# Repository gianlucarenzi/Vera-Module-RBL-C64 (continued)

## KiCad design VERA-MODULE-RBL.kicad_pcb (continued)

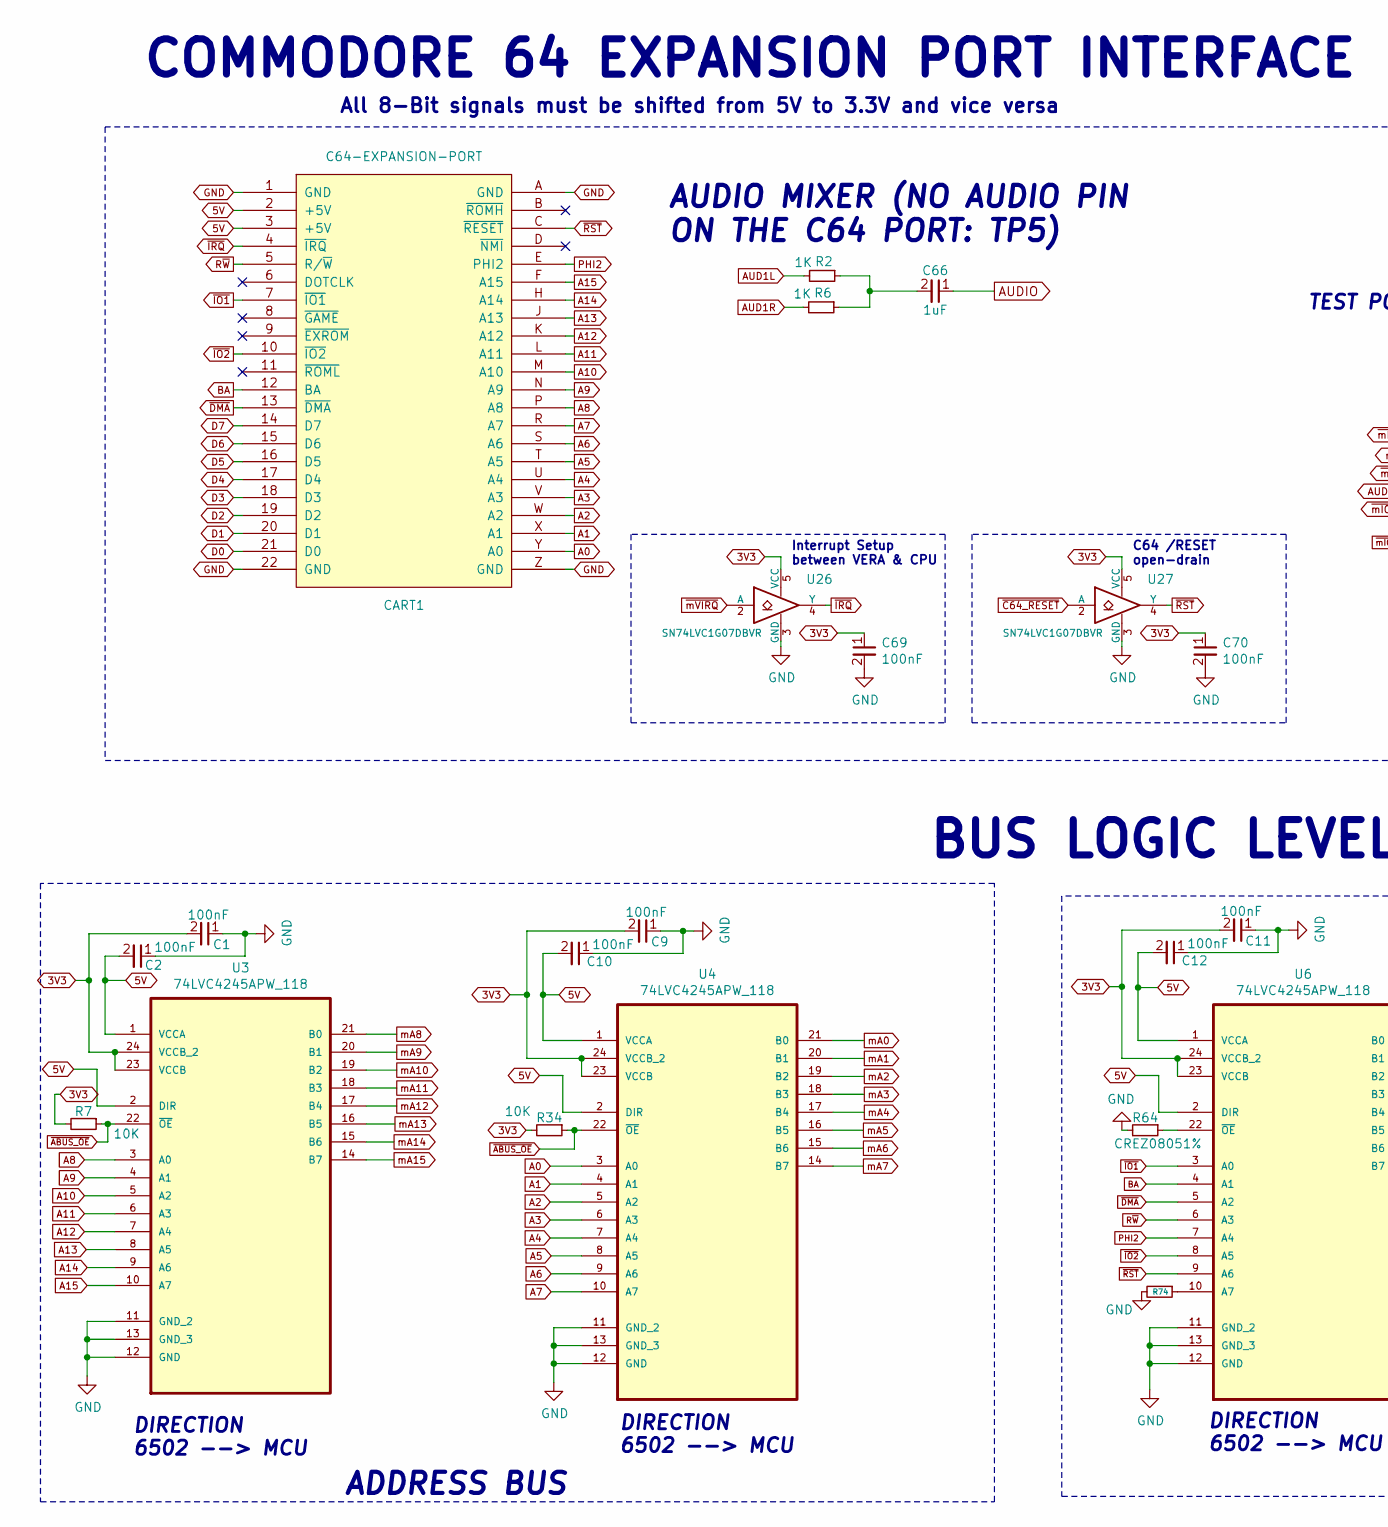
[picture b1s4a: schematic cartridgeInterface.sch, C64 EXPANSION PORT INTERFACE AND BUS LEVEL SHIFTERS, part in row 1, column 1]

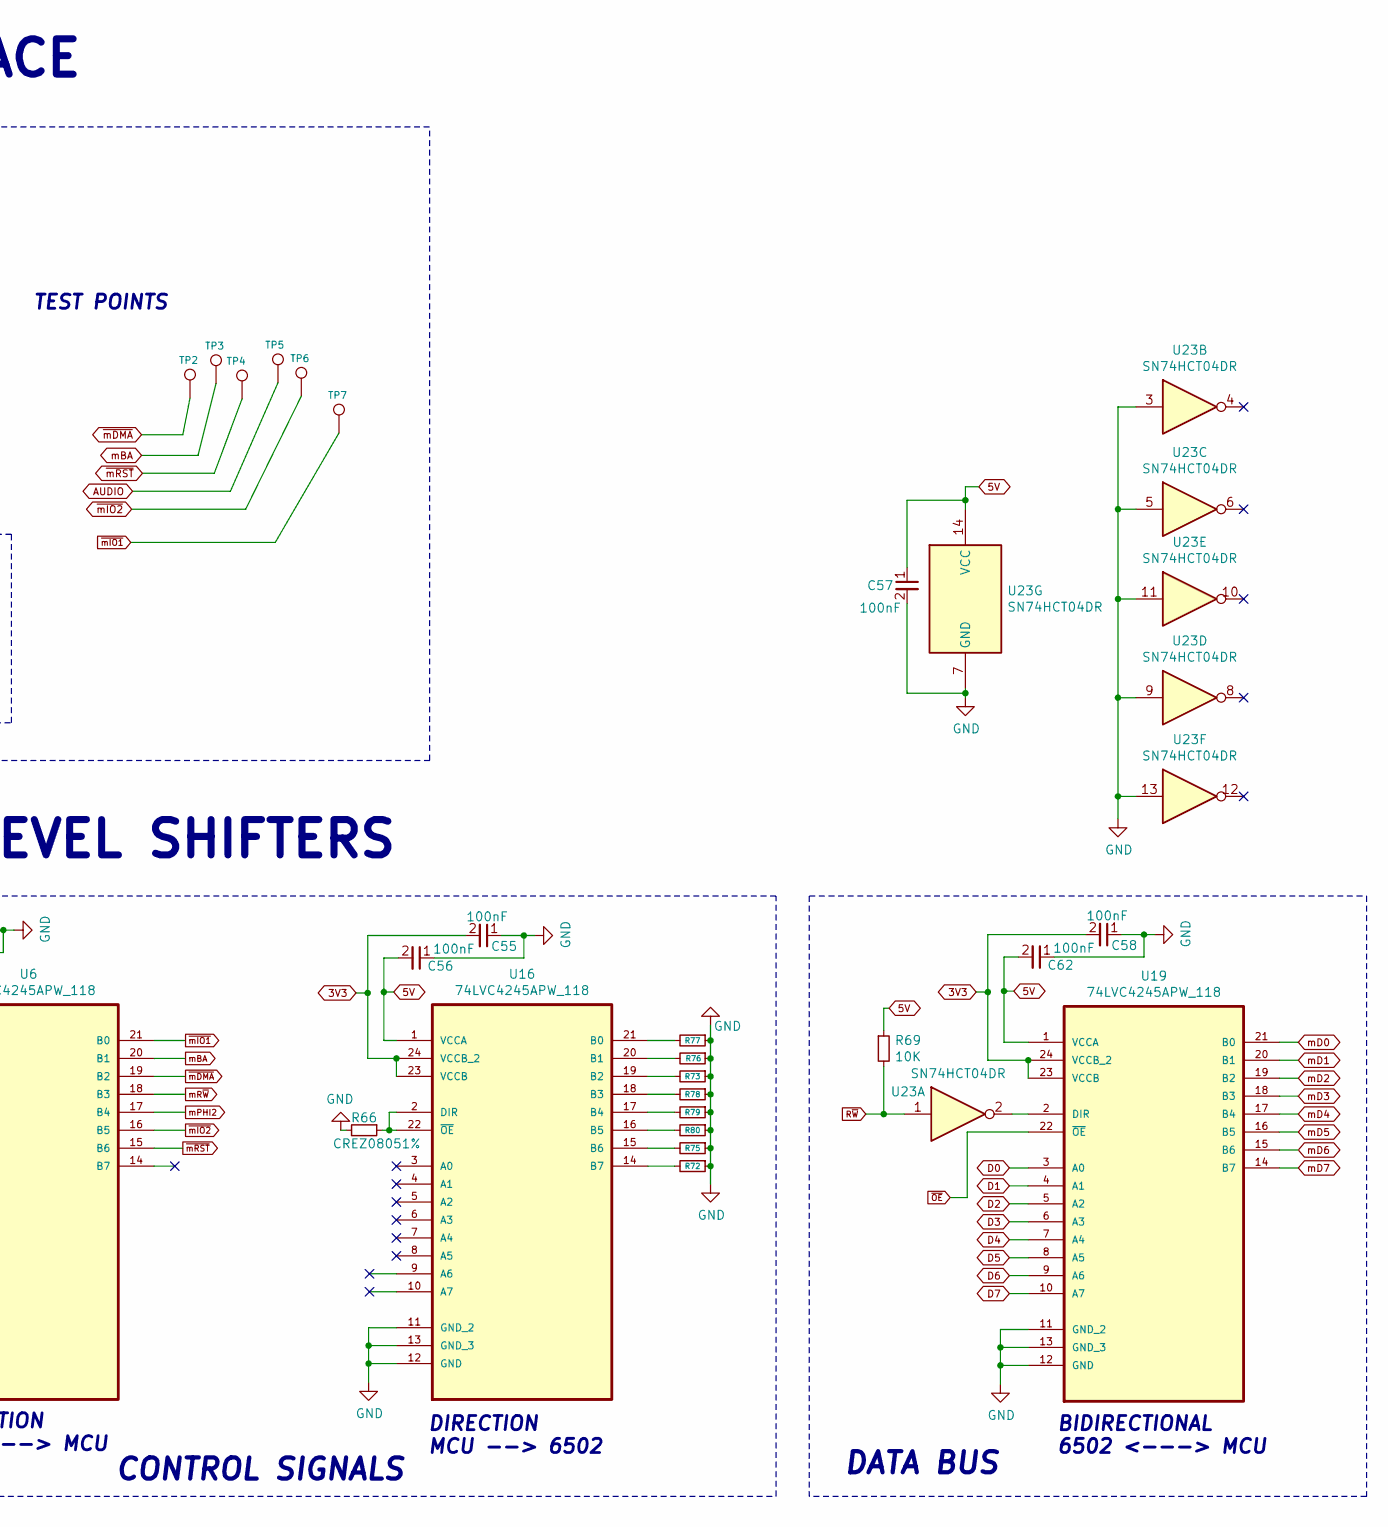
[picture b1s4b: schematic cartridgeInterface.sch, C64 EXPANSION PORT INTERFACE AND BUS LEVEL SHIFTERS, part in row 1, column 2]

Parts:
C1, C2, C9, C10, C11, C12, C55, C56, C57, C58, C62, C69, C70: 100nF; C_0805_2012Metric_Pad1.18x1.45mm_HandSolder; LCSC C28233
C66: 1uF; C_0805_2012Metric_Pad1.18x1.45mm_HandSolder; LCSC C28323
CART1: C64-EXPANSION-PORT; C64-EXPANSION-CARTRIDGE
R2, R6: 1K; R_0805_2012Metric_Pad1.20x1.40mm_HandSolder; LCSC C17513
R7, R34, R69: 10K; R_0805_2012Metric_Pad1.20x1.40mm_HandSolder; LCSC C17414
R64, R66, R72, R73, R74, R75, R76, R77, R78, R79, R80: CREZ08051%; R_0805_2012Metric_Pad1.20x1.40mm_HandSolder; LCSC C17477
TP2, TP3, TP4, TP5, TP6, TP7: TestPoint; TestPoint_Pad_D2.0mm
U3, U4, U6, U16, U19: 74LVC4245APW_118; IC_74LVC4245_SOP65P640X110-24N; LCSC C6091
U23: SN74HCT04DR; SOIC-14_3.9x8.7mm_P1.27mm; LCSC C6766
U26, U27: SN74LVC1G07DBVR; SOT-23-5; LCSC C7829

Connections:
3V3: C1.2, C9.2, C11.2, C55.2, C58.2, C69.1, C70.1, R7.2, R34.2, U3.23 (VCCB), U3.24 (VCCB_2), U4.23 (VCCB), U4.24 (VCCB_2), U6.23 (VCCB), U6.24 (VCCB_2), U16.23 (VCCB), U16.24 (VCCB_2), U19.23 (VCCB), U19.24 (VCCB_2), U26.5 (VCC), U27.5 (VCC); also elsewhere on the board
5V: C2.2, C10.2, C12.2, C56.2, C57.1, C62.2, CART1.2 (+5V), CART1.3 (+5V), R69.1, U3.1 (VCCA), U3.2 (DIR), U4.1 (VCCA), U4.2 (DIR), U6.1 (VCCA), U6.2 (DIR), U16.1 (VCCA), U19.1 (VCCA), U23.14 (VCC); also elsewhere on the board
A0: CART1.Y (A0), U4.3 (A0)
A1: CART1.X (A1), U4.4 (A1)
A2: CART1.W (A2), U4.5 (A2)
A3: CART1.V (A3), U4.6 (A3)
A4: CART1.U (A4), U4.7 (A4)
A5: CART1.T (A5), U4.8 (A5)
A6: CART1.S (A6), U4.9 (A6)
A7: CART1.R (A7), U4.10 (A7)
A8: CART1.P (A8), U3.3 (A0)
A9: CART1.N (A9), U3.4 (A1)
A10: CART1.M (A10), U3.5 (A2)
A11: CART1.L (A11), U3.6 (A3)
A12: CART1.K (A12), U3.7 (A4)
A13: CART1.J (A13), U3.8 (A5)
A14: CART1.H (A14), U3.9 (A6)
A15: CART1.F (A15), U3.10 (A7)
AUD1L: R2.2; also elsewhere on the board
AUD1R: R6.2; also elsewhere on the board
AUDIO: C66.1, TP5.1
BA: CART1.12 (BA), U6.4 (A1)
D0: CART1.21 (D0), U19.3 (A0)
D1: CART1.20 (D1), U19.4 (A1)
D2: CART1.19 (D2), U19.5 (A2)
D3: CART1.18 (D3), U19.6 (A3)
D4: CART1.17 (D4), U19.7 (A4)
D5: CART1.16 (D5), U19.8 (A5)
D6: CART1.15 (D6), U19.9 (A6)
D7: CART1.14 (D7), U19.10 (A7)
GND: C1.1, C2.1, C9.1, C10.1, C11.1, C12.1, C55.1, C56.1, C57.2, C58.1, C62.1, C69.2, C70.2, CART1.1 (GND), CART1.22 (GND), CART1.A (GND), CART1.Z (GND), R64.2, R66.2, R72.1, R73.1, R74.2, R75.1, R76.1, R77.1, R78.1, R79.1, R80.1, U3.11 (GND_2), U3.12 (GND), U3.13 (GND_3), U4.11 (GND_2), U4.12 (GND), U4.13 (GND_3), U6.11 (GND_2), U6.12 (GND), U6.13 (GND_3), U16.11 (GND_2), U16.12 (GND), U16.13 (GND_3), U19.11 (GND_2), U19.12 (GND), U19.13 (GND_3), U23.3, U23.5, U23.7 (GND), U23.9, U23.11, U23.13, U26.3 (GND), U27.3 (GND); also elsewhere on the board
unnamed: C66.2, R2.1, R6.1
unnamed: R64.1, U6.22 (~OE)
unnamed: R66.1, U16.2 (DIR), U16.22 (~OE)
unnamed: R72.2, U16.14 (B7)
unnamed: R73.2, U16.19 (B2)
unnamed: R74.1, U6.10 (A7)
unnamed: R75.2, U16.15 (B6)
unnamed: R76.2, U16.20 (B1)
unnamed: R77.2, U16.21 (B0)
unnamed: R78.2, U16.18 (B3)
unnamed: R79.2, U16.17 (B4)
unnamed: R80.2, U16.16 (B5)
unnamed: U19.2 (DIR), U23.2
PHI2: CART1.E (PHI2), U6.7 (A4)
R~W: CART1.5 (R/~W), R69.2, U6.6 (A3), U23.1
mA0: U4.21 (B0); also elsewhere on the board
mA1: U4.20 (B1); also elsewhere on the board
mA2: U4.19 (B2); also elsewhere on the board
mA3: U4.18 (B3); also elsewhere on the board
mA4: U4.17 (B4); also elsewhere on the board
mA5: U4.16 (B5); also elsewhere on the board
mA6: U4.15 (B6); also elsewhere on the board
mA7: U4.14 (B7); also elsewhere on the board
mA8: U3.21 (B0); also elsewhere on the board
mA9: U3.20 (B1); also elsewhere on the board
mA10: U3.19 (B2); also elsewhere on the board
mA11: U3.18 (B3); also elsewhere on the board
mA12: U3.17 (B4); also elsewhere on the board
mA13: U3.16 (B5); also elsewhere on the board
mA14: U3.15 (B6); also elsewhere on the board
mA15: U3.14 (B7); also elsewhere on the board
mBA: TP3.1, U6.20 (B1)
mD0: U19.21 (B0); also elsewhere on the board
mD1: U19.20 (B1); also elsewhere on the board
mD2: U19.19 (B2); also elsewhere on the board
mD3: U19.18 (B3); also elsewhere on the board
mD4: U19.17 (B4); also elsewhere on the board
mD5: U19.16 (B5); also elsewhere on the board
mD6: U19.15 (B6); also elsewhere on the board
mD7: U19.14 (B7); also elsewhere on the board
mPHI2: U6.17 (B4); also elsewhere on the board
mR~W: U6.18 (B3); also elsewhere on the board
~ABUS_OE: R7.1, R34.1, U3.22 (~OE), U4.22 (~OE); also elsewhere on the board
~C64_RESET: U27.2 (A); also elsewhere on the board
~DMA: CART1.13 (~DMA), U6.5 (A2)
~IO1: CART1.7 (~IO1), U6.3 (A0)
~IO2: CART1.10 (~IO2), U6.8 (A5)
~IRQ: CART1.4 (~IRQ), U26.4 (Y)
~OE: U19.22 (~OE); also elsewhere on the board
~RST: CART1.C (~RESET), U6.9 (A6), U27.4 (Y)
~mDMA: TP2.1, U6.19 (B2)
~mIO1: TP7.1, U6.21 (B0); also elsewhere on the board
~mIO2: TP6.1, U6.16 (B5); also elsewhere on the board
~mRST: TP4.1, U6.15 (B6)
~mVIRQ: U26.2 (A); also elsewhere on the board

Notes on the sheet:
COMMODORE 64 EXPANSION PORT INTERFACE
All 8-Bit signals must be shifted from 5V to 3.3V and vice versa
TEST POINTS
BUS LOGIC LEVEL SHIFTERS
DIRECTION 6502 --> MCU
DIRECTION MCU --> 6502
BIDIRECTIONAL 6502 <---> MCU
CONTROL SIGNALS
ADDRESS BUS
DATA BUS
Interrupt Setup between VERA & CPU
C64 /RESET open-drain
AUDIO MIXER (NO AUDIO PIN ON THE C64 PORT: TP5)

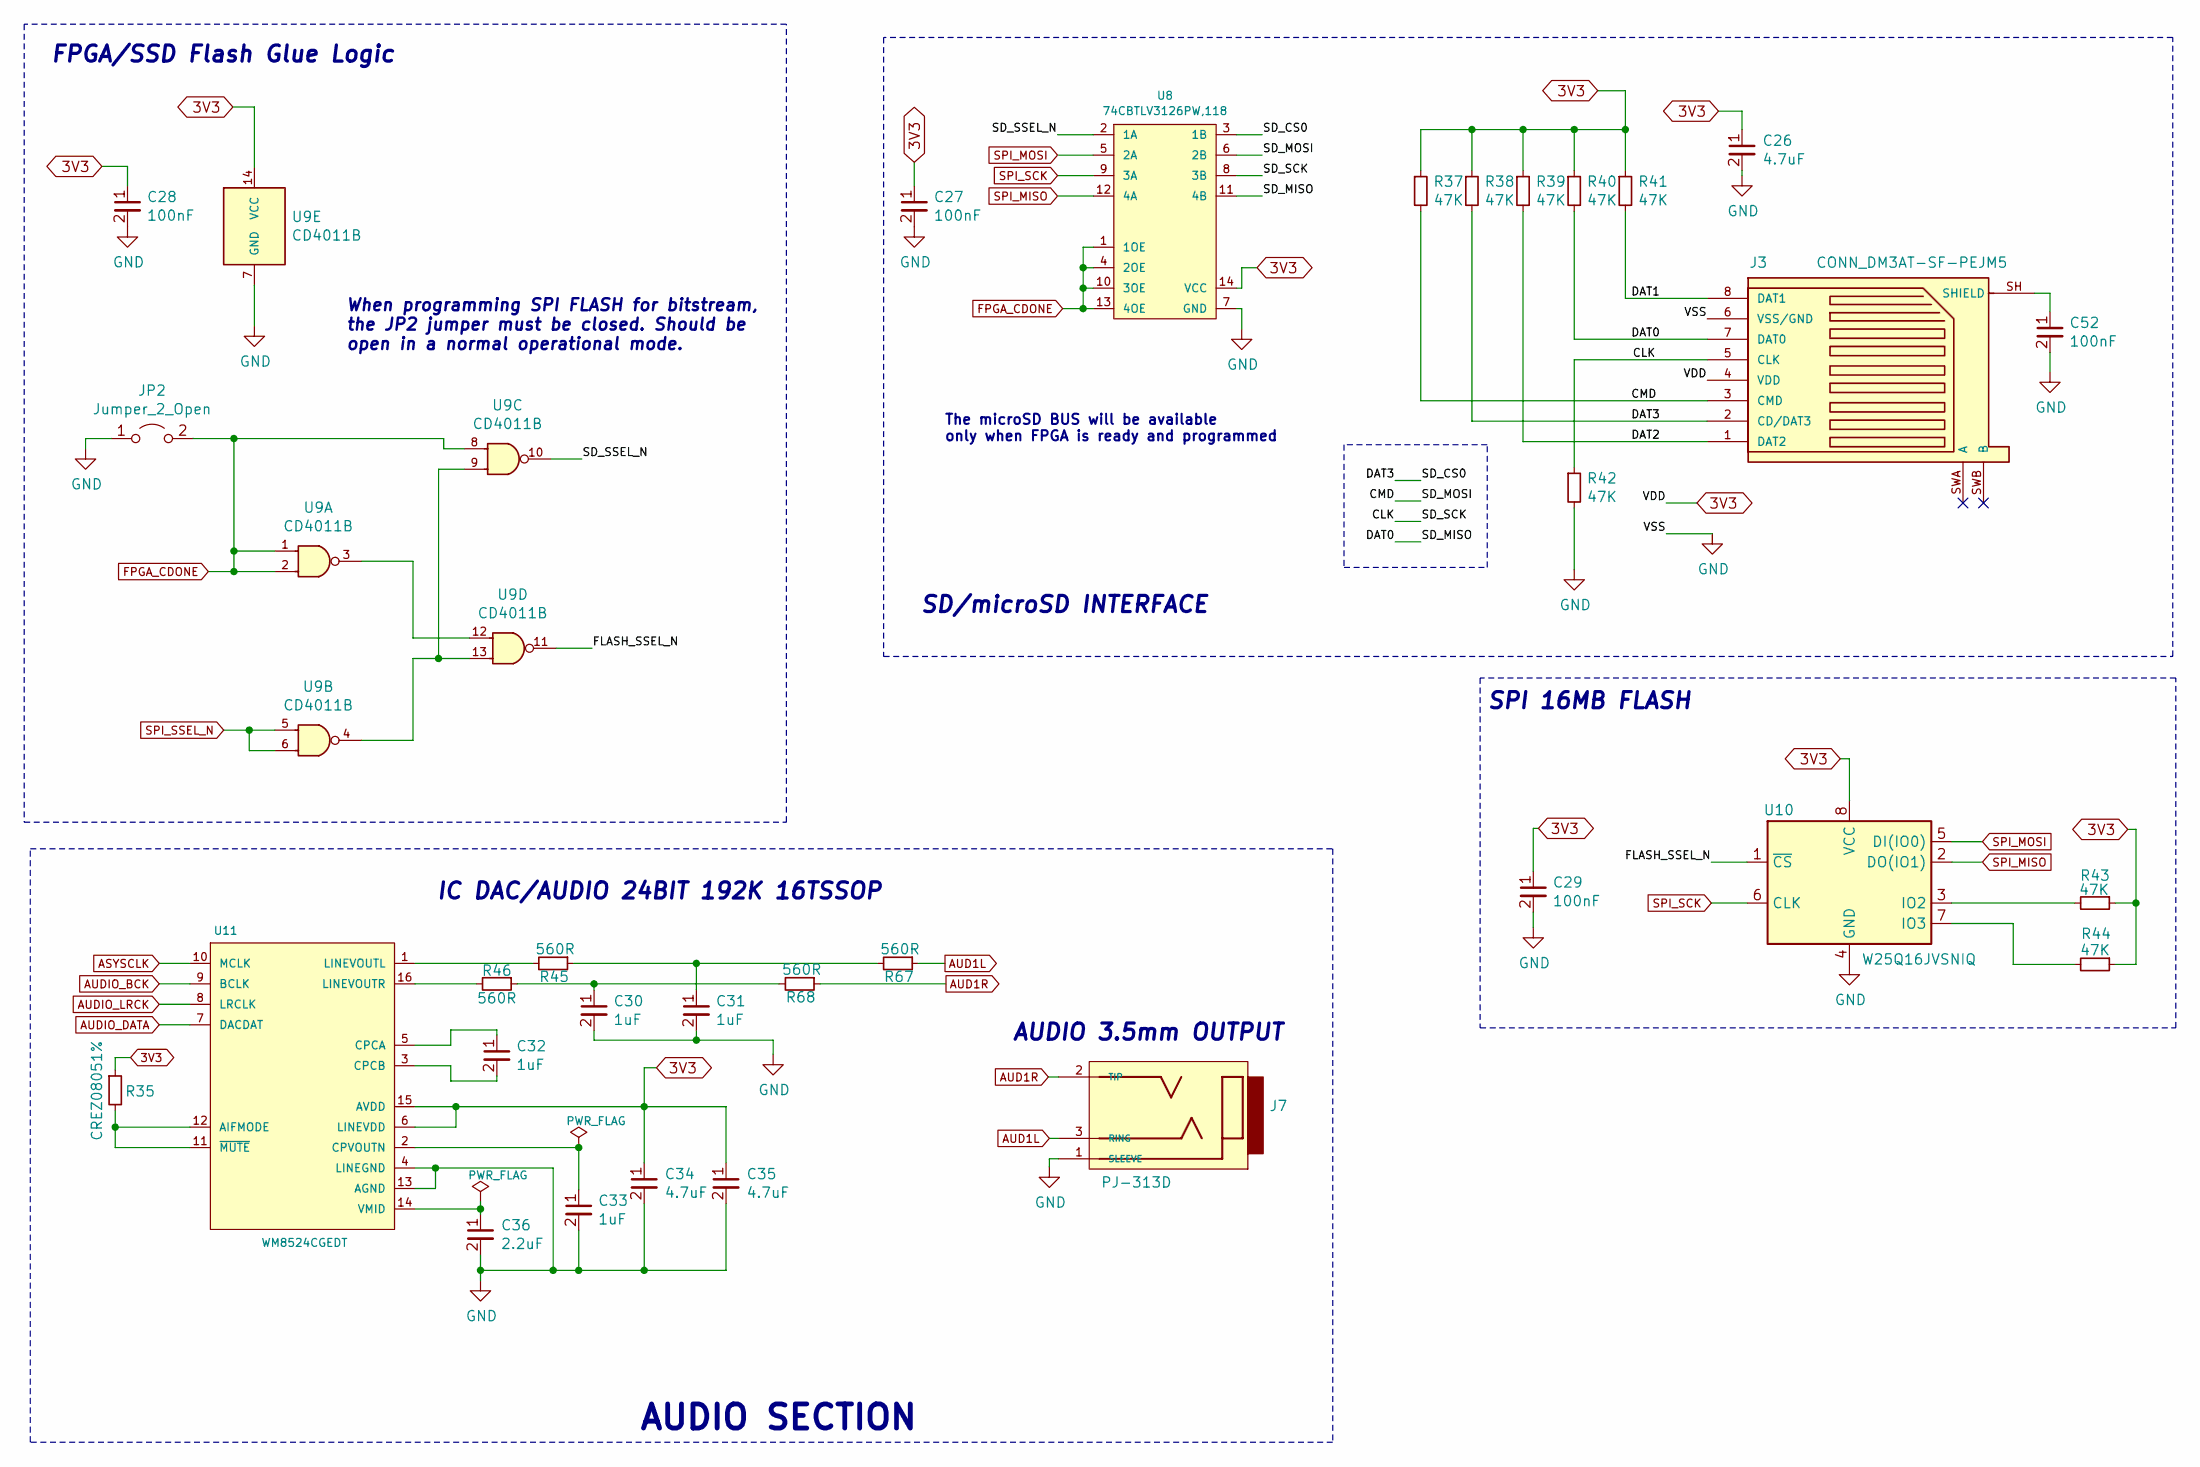
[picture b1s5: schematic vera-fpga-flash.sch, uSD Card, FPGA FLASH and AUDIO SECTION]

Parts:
C26, C34, C35: 4.7uF; C_0805_2012Metric_Pad1.18x1.45mm_HandSolder; LCSC C1779
C27, C28, C29, C52: 100nF; C_0805_2012Metric_Pad1.18x1.45mm_HandSolder; LCSC C28233
C30, C31, C32, C33: 1uF; C_0805_2012Metric_Pad1.18x1.45mm_HandSolder; LCSC C28323
C36: 2.2uF; C_0805_2012Metric_Pad1.18x1.45mm_HandSolder; LCSC C377773
J3: CONN_DM3AT-SF-PEJM5; HRS_DM3AT-SF-PEJM5; PARTREV 20200913; LCSC C114218
J7: PJ-313D; jack_3.5_pj313d-smt; LCSC C668608
JP2: Jumper_2_Open; PinHeader_1x02_P2.54mm_Vertical
R35: CREZ08051%; R_0805_2012Metric_Pad1.20x1.40mm_HandSolder; LCSC C17477
R37, R38, R39, R40, R41, R42, R43, R44: 47K; R_0805_2012Metric_Pad1.20x1.40mm_HandSolder; LCSC C17713
R45, R46, R67, R68: 560R; R_0805_2012Metric_Pad1.20x1.40mm_HandSolder; LCSC C28636
U8: 74CBTLV3126PW,118; TSSOP-14_4.4x5mm_P0.65mm; LCSC C543078
U9: CD4011B; SOIC-14_3.9x8.7mm_P1.27mm; LCSC C194334
U10: W25Q16JVSNIQ; SOIC-8_3.9x4.9mm_P1.27mm; LCSC C2456211
U11: WM8524CGEDT; TSSOP-16_4.4x5mm_P0.65mm; LCSC C146242

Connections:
3V3: C26.1, C27.1, C28.1, C29.1, C34.1, C35.1, J3.4 (VDD), R35.1, R37.1, R38.1, R39.1, R40.1, R41.1, R43.1, R44.1, U8.14 (VCC), U9.14 (VCC), U10.8 (VCC), U11.6 (LINEVDD), U11.15 (AVDD); also elsewhere on the board
/Vera FPGA flash/CLK: J3.5 (CLK), R42.1, U8.8 (3B)
/Vera FPGA flash/CMD: J3.3 (CMD), R37.2, U8.6 (2B)
/Vera FPGA flash/DAT0: J3.7 (DAT0), R40.2, U8.11 (4B)
/Vera FPGA flash/DAT1: J3.8 (DAT1), R41.2
/Vera FPGA flash/DAT2: J3.1 (DAT2), R39.2
/Vera FPGA flash/DAT3: J3.2 (CD/DAT3), R38.2, U8.3 (1B)
/Vera FPGA flash/FLASH_SSEL_N: U9.11 (4Y), U10.1 (~CS)
/Vera FPGA flash/SD_SSEL_N: U8.2 (1A), U9.10 (4Y)
ASYSCLK: U11.10 (MCLK); also elsewhere on the board
AUD1L: J7.3 (RING), R67.1; also elsewhere on the board
AUD1R: J7.2 (TIP), R68.1; also elsewhere on the board
AUDIO_BCK: U11.9 (BCLK); also elsewhere on the board
AUDIO_DATA: U11.7 (DACDAT); also elsewhere on the board
AUDIO_LRCK: U11.8 (LRCLK); also elsewhere on the board
FPGA_CDONE: JP2.2 (B), U8.1 (1OE), U8.4 (2OE), U8.10 (3OE), U8.13 (4OE), U9.1 (4A), U9.2 (4B), U9.8 (4A); also elsewhere on the board
GND: C26.2, C27.2, C28.2, C29.2, C30.2, C31.2, C33.2, C34.2, C35.2, C36.2, C52.2, J3.6 (VSS/GND), J7.1 (SLEEVE), JP2.1 (A), R42.2, U8.7 (GND), U9.7 (GND), U10.4 (GND), U11.4 (LINEGND), U11.13 (AGND); also elsewhere on the board
unnamed: C30.1, R46.1, R68.2
unnamed: C31.1, R45.1, R67.2
unnamed: C32.1, U11.5 (CPCA)
unnamed: C32.2, U11.3 (CPCB)
unnamed: C33.1, U11.2 (CPVOUTN)
unnamed: C36.1, U11.14 (VMID)
unnamed: C52.1, J3.SH (SHIELD)
unnamed: R35.2, U11.11 (~MUTE), U11.12 (AIFMODE)
unnamed: R43.2, U10.3 (IO2)
unnamed: R44.2, U10.7 (IO3)
unnamed: R45.2, U11.1 (LINEVOUTL)
unnamed: R46.2, U11.16 (LINEVOUTR)
unnamed: U9.3 (4Y), U9.12 (4A)
unnamed: U9.4 (4Y), U9.9 (4B), U9.13 (4B)
SPI_MISO: U8.12 (4A), U10.2 (DO(IO1)); also elsewhere on the board
SPI_MOSI: U8.5 (2A), U10.5 (DI(IO0)); also elsewhere on the board
SPI_SCK: U8.9 (3A), U10.6 (CLK); also elsewhere on the board
SPI_SSEL_N: U9.5 (4A), U9.6 (4B); also elsewhere on the board

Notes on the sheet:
IC DAC/AUDIO 24BIT 192K 16TSSOP
SD/microSD INTERFACE
FPGA/SSD Flash Glue Logic
SPI 16MB FLASH
The microSD BUS will be available only when FPGA is ready and programmed
When programming SPI FLASH for bitstream, the JP2 jumper must be closed. Should be open in a normal operational mode.
AUDIO 3.5mm OUTPUT
AUDIO SECTION

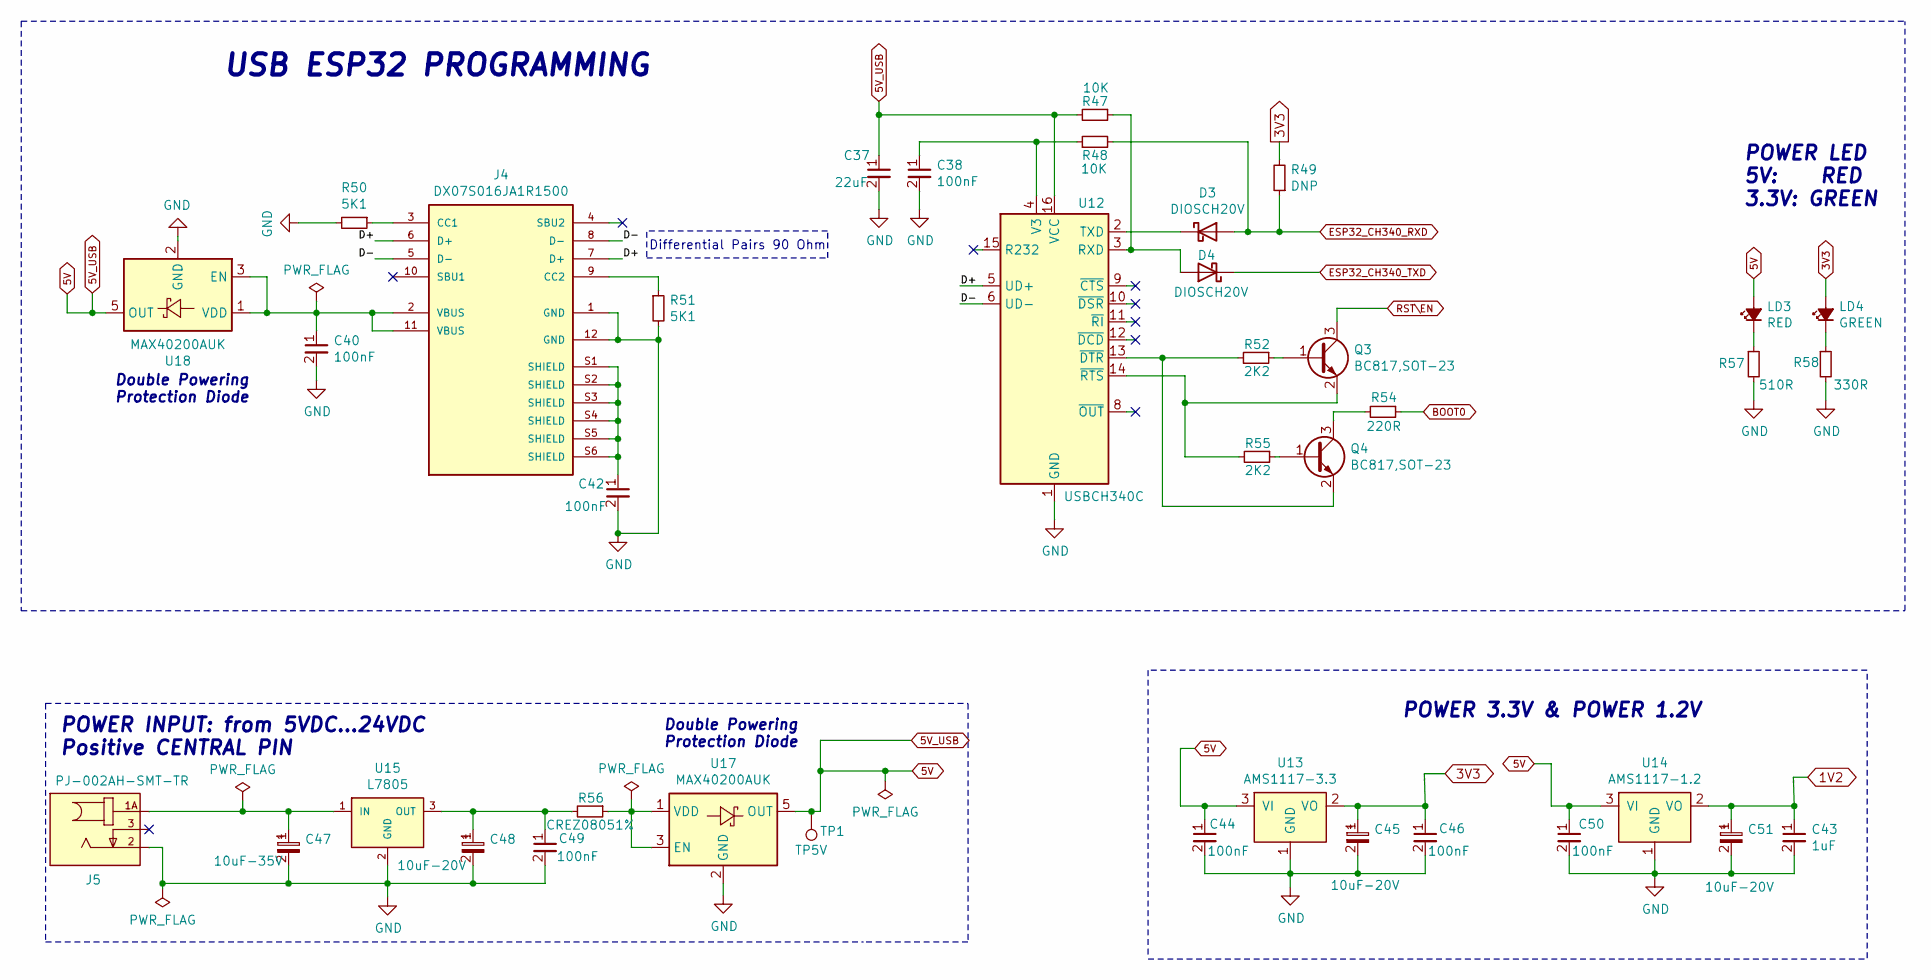
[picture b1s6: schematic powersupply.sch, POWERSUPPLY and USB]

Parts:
C37: 22uF; C_0805_2012Metric_Pad1.18x1.45mm_HandSolder; LCSC C45783
C38, C40, C42, C44, C46, C49, C50: 100nF; C_0805_2012Metric_Pad1.18x1.45mm_HandSolder; LCSC C28233
C43: 1uF; C_0805_2012Metric_Pad1.18x1.45mm_HandSolder; LCSC C28323
C45, C48, C51: 10uF-20V; CP_EIA-3528-12_Kemet-T_Pad1.50x2.35mm_HandSolder; LCSC C8017
C47: 10uF-35V; CP_EIA-3528-12_Kemet-T_Pad1.50x2.35mm_HandSolder; LCSC C5346021
D3, D4: DIOSCH20V; D_SMC_Handsoldering; LCSC C236151
J4: DX07S016JA1R1500; JAE_DX07S016JA1R1500; PARTREV 1; LCSC C3197885
J5: PJ-002AH-SMT-TR; CUI_PJ-002AH-SMT-TR; LCSC C22434687
LD3: RED; LED_1206_3216Metric_Pad1.42x1.75mm_HandSolder; LCSC C965822
LD4: GREEN; LED_0805_2012Metric_Pad1.15x1.40mm_HandSolder; LCSC C2297
Q3, Q4: BC817,SOT-23; SOT-23; LCSC C20069154
R47, R48: 10K; R_0805_2012Metric_Pad1.20x1.40mm_HandSolder; LCSC C17414
R49: DNP; R_1206_3216Metric_Pad1.30x1.75mm_HandSolder
R50, R51: 5K1; R_0805_2012Metric_Pad1.20x1.40mm_HandSolder; LCSC C27834
R52, R55: 2K2; R_0805_2012Metric_Pad1.20x1.40mm_HandSolder; LCSC C17520
R54: 220R; R_0805_2012Metric_Pad1.20x1.40mm_HandSolder; LCSC C17557
R56: CREZ08051%; R_0805_2012Metric_Pad1.20x1.40mm_HandSolder; LCSC C17477
R57: 510R; R_0805_2012Metric_Pad1.20x1.40mm_HandSolder; LCSC C17734
R58: 330R; R_0603_1608Metric_Pad0.98x0.95mm_HandSolder; LCSC C23138
TP1: TP5V; TestPoint_Pad_D2.0mm
U12: USBCH340C; SOIC-16_3.9x9.9mm_P1.27mm; LCSC C84681
U13: AMS1117-3.3; SOT-223-3_TabPin2; LCSC C6186
U14: AMS1117-1.2; SOT-223-3_TabPin2; LCSC C347218
U15: L7805; TO-252-2; LCSC C110908
U17, U18: MAX40200AUK; SOT-23-5; LCSC C47118006

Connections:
1V2: C43.1, C51.1, U14.2 (VO); also elsewhere on the board
3V3: C45.1, C46.1, LD4.2 (A), R49.2, U13.2 (VO); also elsewhere on the board
5V: C37.1, C44.1, C50.1, LD3.2 (A), R47.2, TP1.1, U12.16 (VCC), U13.3 (VI), U14.3 (VI), U17.5 (OUT), U18.5 (OUT); also elsewhere on the board
/PowerSupply/D+: J4.6 (D+), J4.7 (D+), U12.5 (UD+)
/PowerSupply/D-: J4.5 (D-), J4.8 (D-), U12.6 (UD-)
BOOT0: R54.1; also elsewhere on the board
ESP32_CH340_RXD: D3.2 (A), R48.2, R49.1; also elsewhere on the board
ESP32_CH340_TXD: D4.1 (K); also elsewhere on the board
GND: C37.2, C38.2, C40.2, C42.2, C43.2, C44.2, C45.2, C46.2, C47.2, C48.2, C49.2, C50.2, C51.2, J4.1 (GND), J4.12 (GND), J5.2, R50.2, R51.2, R57.2, R58.2, U12.1 (GND), U13.1 (GND), U14.1 (GND), U15.2 (GND), U17.2 (GND), U18.2 (GND); also elsewhere on the board
unnamed: C38.1, R48.1, U12.4 (V3)
unnamed: C40.1, J4.2 (VBUS), J4.11 (VBUS), U18.1 (VDD), U18.3 (EN)
unnamed: C42.1, J4.S1 (SHIELD), J4.S2 (SHIELD), J4.S3 (SHIELD), J4.S4 (SHIELD), J4.S5 (SHIELD), J4.S6 (SHIELD)
unnamed: C47.1, J5.1A, J5.1B, U15.1 (IN)
unnamed: C48.1, C49.1, R56.2, U15.3 (OUT)
unnamed: D3.1 (K), U12.2 (TXD)
unnamed: D4.2 (A), R47.1, U12.3 (RXD)
unnamed: J4.3 (CC1), R50.1
unnamed: J4.9 (CC2), R51.1
unnamed: LD3.1 (K), R57.1
unnamed: LD4.1 (K), R58.1
unnamed: Q3.1 (B), R52.1
unnamed: Q3.2 (E), R55.2, U12.14 (~RTS)
unnamed: Q4.1 (B), R55.1
unnamed: Q4.2 (E), R52.2, U12.13 (~DTR)
unnamed: Q4.3 (C), R54.2
unnamed: R56.1, U17.1 (VDD), U17.3 (EN)
RST\EN: Q3.3 (C); also elsewhere on the board

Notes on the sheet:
POWER INPUT: from 5VDC...24VDC Positive CENTRAL PIN
USB ESP32 PROGRAMMING
POWER 3.3V & POWER 1.2V
POWER LED 5V: RED 3.3V: GREEN
Differential Pairs 90 Ohm
Double Powering Protection Diode

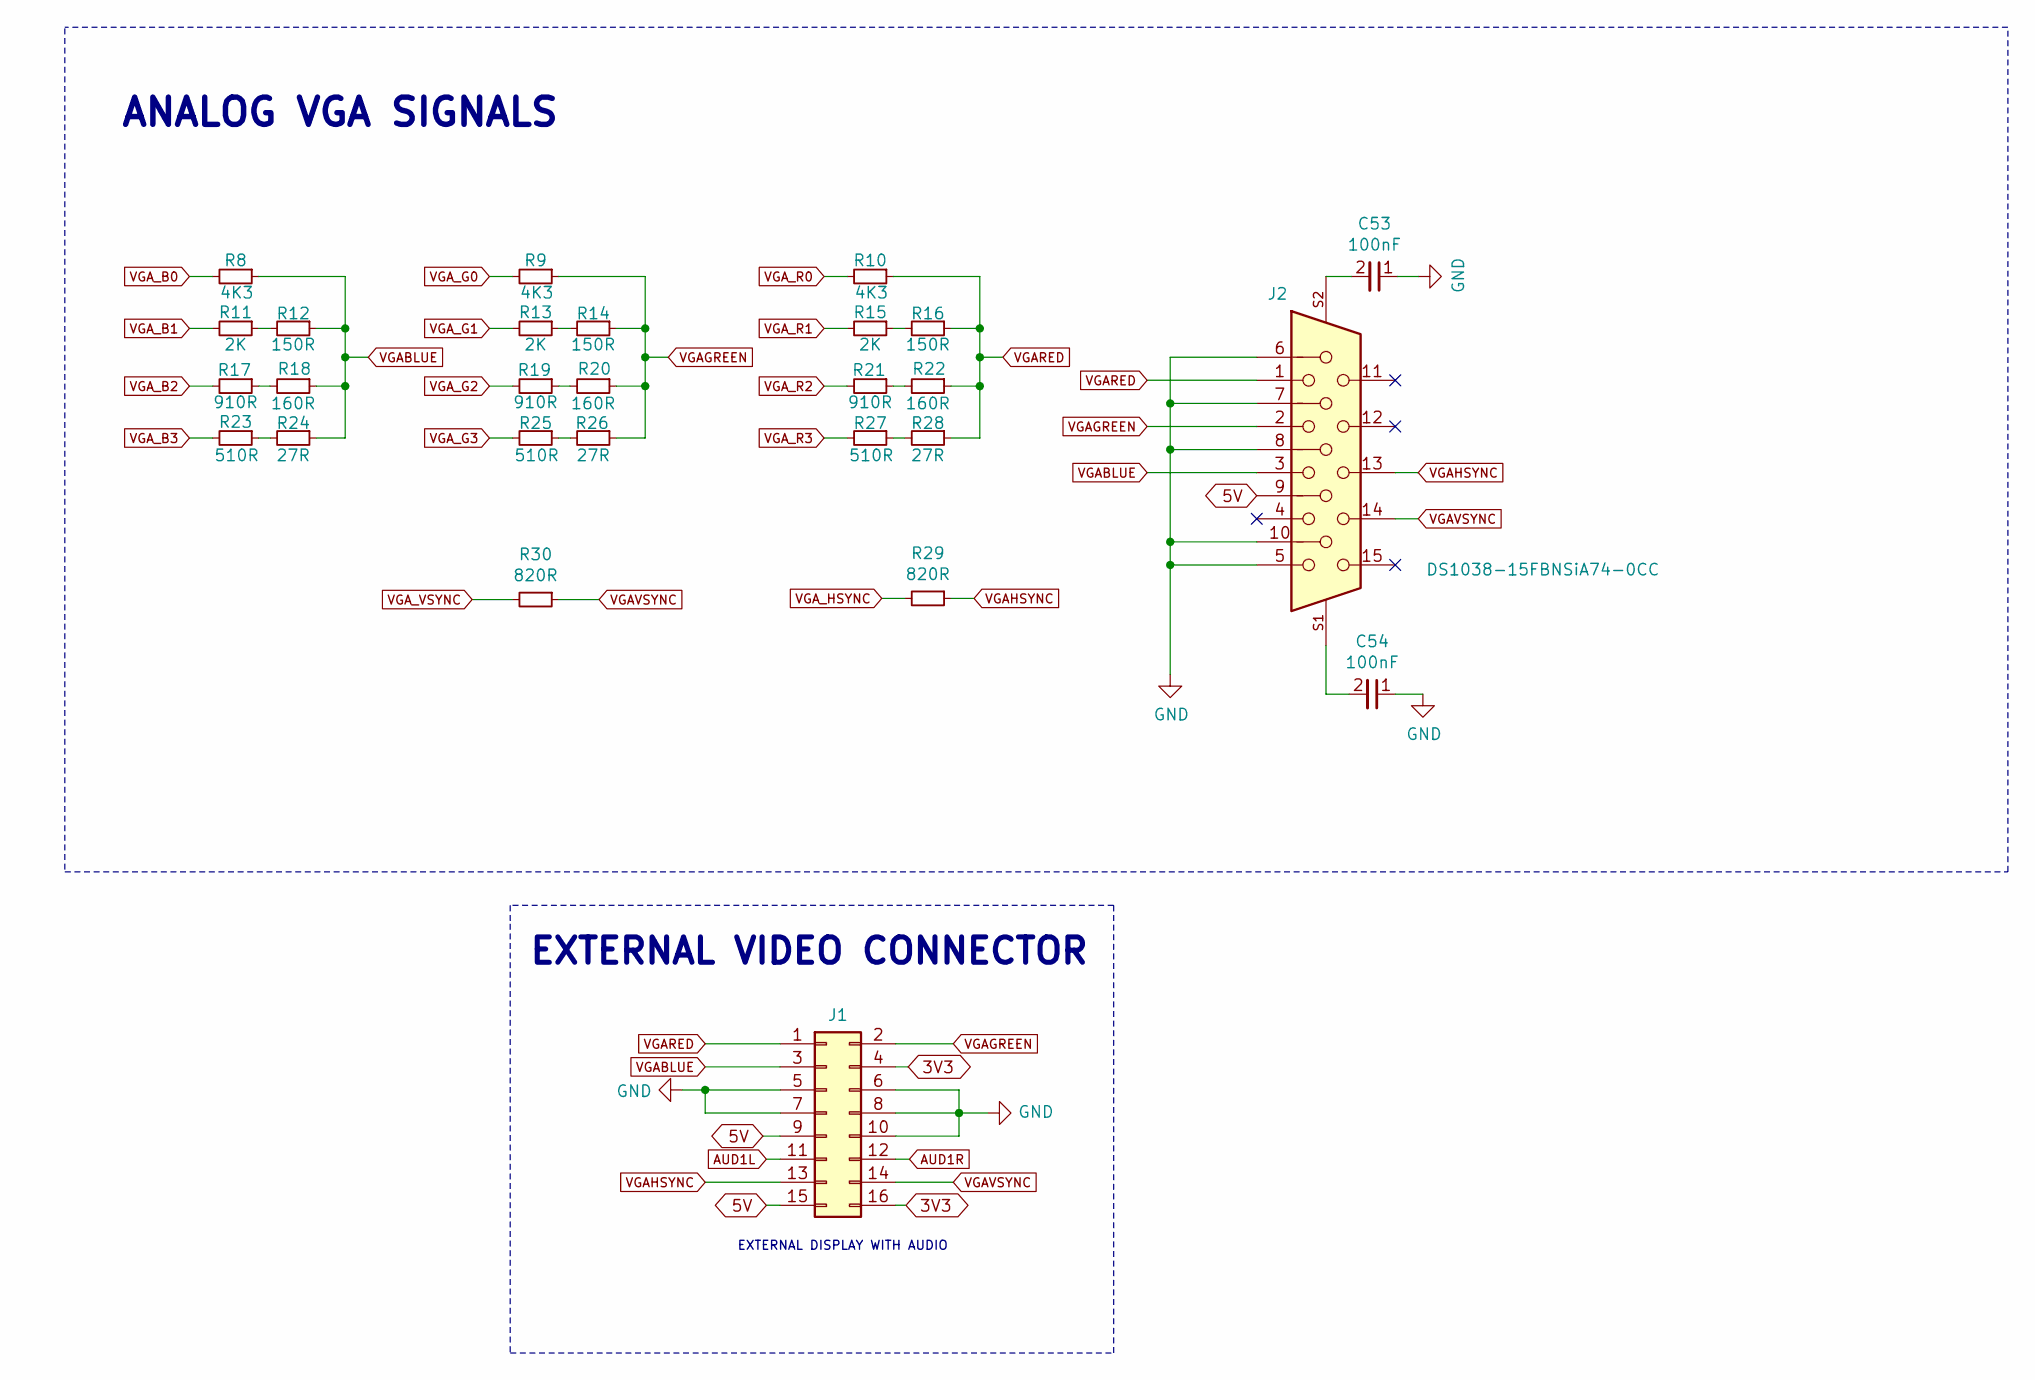
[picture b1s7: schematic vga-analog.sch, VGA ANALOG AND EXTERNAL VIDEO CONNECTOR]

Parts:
C53, C54: 100nF; C_0805_2012Metric_Pad1.18x1.45mm_HandSolder; LCSC C28233
J1: CONN_SMD_HEADER_BOX_02x08_HX-JN2.54; IDC-Header_2x08_P2.54mm_Vertical_SMD; LCSC C41376031
J2: DS1038-15FBNSiA74-0CC; CONNFLY_DS1038-15FBNSIA74-0CC; LCSC C75754
R8, R9, R10: 4K3; R_0805_2012Metric_Pad1.20x1.40mm_HandSolder; LCSC C17667
R11, R13, R15: 2K; R_0805_2012Metric_Pad1.20x1.40mm_HandSolder; LCSC C17604
R12, R14, R16: 150R; R_0805_2012Metric_Pad1.20x1.40mm_HandSolder; LCSC C17471
R17, R19, R21: 910R; R_0805_2012Metric_Pad1.20x1.40mm_HandSolder; LCSC C2930211
R18, R20, R22: 160R; R_0805_2012Metric_Pad1.20x1.40mm_HandSolder; LCSC C2960793
R23, R25, R27: 510R; R_0805_2012Metric_Pad1.20x1.40mm_HandSolder; LCSC C17734
R24, R26, R28: 27R; R_0805_2012Metric_Pad1.20x1.40mm_HandSolder; LCSC C17594
R29, R30: 820R; R_0805_2012Metric_Pad1.20x1.40mm_HandSolder; LCSC C17837

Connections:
3V3: J1.4, J1.16; also elsewhere on the board
5V: J1.9, J1.15, J2.9; also elsewhere on the board
AUD1L: J1.11; also elsewhere on the board
AUD1R: J1.12; also elsewhere on the board
GND: C53.1, C54.1, J1.5, J1.6, J1.7, J1.8, J1.10, J2.5, J2.6, J2.7, J2.8, J2.10; also elsewhere on the board
unnamed: C53.2, J2.S2 (SHIELD__1)
unnamed: C54.2, J2.S1 (SHIELD)
unnamed: R11.1, R12.2
unnamed: R13.1, R14.2
unnamed: R15.1, R16.2
unnamed: R17.1, R18.2
unnamed: R19.1, R20.2
unnamed: R21.1, R22.2
unnamed: R23.1, R24.2
unnamed: R25.1, R26.2
unnamed: R27.1, R28.2
VGABLUE: J1.3, J2.3, R8.1, R12.1, R18.1, R24.1
VGAGREEN: J1.2, J2.2, R9.1, R14.1, R20.1, R26.1
VGAHSYNC: J1.13, J2.13, R29.1
VGARED: J1.1, J2.1, R10.1, R16.1, R22.1, R28.1
VGAVSYNC: J1.14, J2.14, R30.1
VGA_B0: R8.2; also elsewhere on the board
VGA_B1: R11.2; also elsewhere on the board
VGA_B2: R17.2; also elsewhere on the board
VGA_B3: R23.2; also elsewhere on the board
VGA_G0: R9.2; also elsewhere on the board
VGA_G1: R13.2; also elsewhere on the board
VGA_G2: R19.2; also elsewhere on the board
VGA_G3: R25.2; also elsewhere on the board
VGA_HSYNC: R29.2; also elsewhere on the board
VGA_R0: R10.2; also elsewhere on the board
VGA_R1: R15.2; also elsewhere on the board
VGA_R2: R21.2; also elsewhere on the board
VGA_R3: R27.2; also elsewhere on the board
VGA_VSYNC: R30.2; also elsewhere on the board

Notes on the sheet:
EXTERNAL DISPLAY WITH AUDIO
ANALOG VGA SIGNALS
EXTERNAL VIDEO CONNECTOR
